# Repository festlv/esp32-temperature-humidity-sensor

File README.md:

# ESP32 environment sensor

This project encompasses hardware and firmware for a WiFi-enabled temperature and humidity sensor.
It has a battery life of ~3 months on a single lithium-ion battery (3000mAh), by reporting temperature and humidity every 15 minutes.

Documentation is a little bit sparse, as this project is for my personal use.

# Recommended hardware changes

After rev1 hardware was built, I realized a few things:
* Either don't use resistor divider to measure battery voltage, or connect it only when awake via transistor (it consumes ~25uA).
* Change MIC5504 voltage regulator to one with less leakage current- it consumes ~40uA.

# Pictures

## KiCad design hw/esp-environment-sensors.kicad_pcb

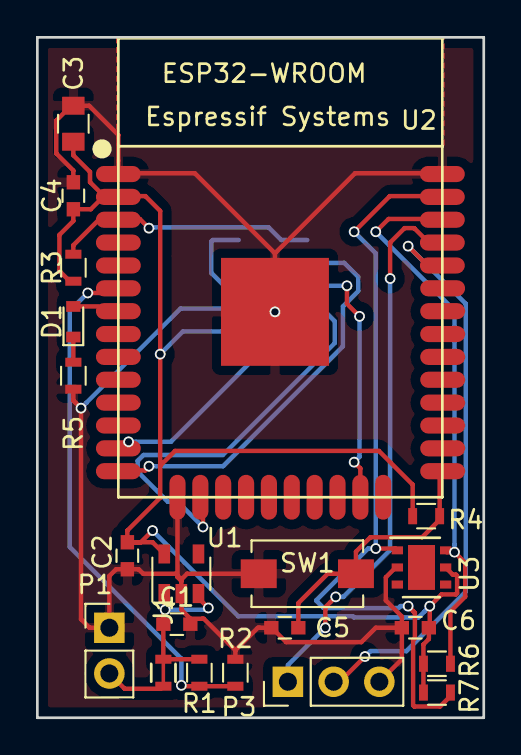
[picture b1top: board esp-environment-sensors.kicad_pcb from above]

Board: 2 copper layers, 24.8 x 37.8 mm, 22 parts (1 on the bottom side), 17 nets.

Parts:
C1, C2, C6: 1uF; C_0603
C3: 22uF; C_0805
C4, C5: 0.1uF; C_0603
D1: LED; D_0603
J1: SB_NC
P1: PWR; Pin_Header_Straight_1x02_Pitch2.54mm
P2: CONN_JTAG; Pin_Header_1.27mm_2x5
P3: DBG; Pin_Header_Straight_1x03_Pitch2.54mm
R1: 47K; R_0603
R2: 100K; R_0603
R3, R4: 10K; R_0603
R5: 220R; R_0603
R6, R7: 2K2; R_0603
SW1: BTN0; SW_SPST_EVQPE1
U1: MIC5504; SOT-23-5
U2: ESP32-WROOM
U3: Si7021; DFN-6-1EP_3x3mm_Pitch0.95mm

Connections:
+3V3: C2.1, C3.1, C4.1, C6.1, P2.1, R3.1, R4.1, R6.1, R7.1, U1.5, U2.2, U3.5
/I2C1_SCL: R7.2, U2.36, U3.6
/I2C1_SDA: R6.2, U2.37, U3.1
/IO0: C5.2, R4.2, SW1.1, U2.25
/N_RST: P2.10, R3.2, U2.3
/RXD0: P3.2, U2.34
/TCK: P2.4, U2.16
/TDI: P2.8, U2.14
/TDO: P2.6, U2.23
/TMS: P2.2, U2.13
/TXD0: P3.1, U2.35
/V_ADC: R1.2, R2.1, U2.6
GND: C1.2, C2.2, C3.2, C4.2, C5.1, C6.2, P1.1, P2.3, P2.5, P2.9, P3.3, R2.2, R5.2, SW1.2, U1.2, U2.1, U2.15, U2.38, U2.39, U3.2
unnamed: D1.1, R5.1
unnamed: D1.2, U2.7
unnamed: J1.2, P1.2
VPP: C1.1, J1.1, R1.1, U1.1, U1.3

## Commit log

2017-12-27 Initial commit (after cleaning up committed sensitive stuff)
2017-12-27 Add license
